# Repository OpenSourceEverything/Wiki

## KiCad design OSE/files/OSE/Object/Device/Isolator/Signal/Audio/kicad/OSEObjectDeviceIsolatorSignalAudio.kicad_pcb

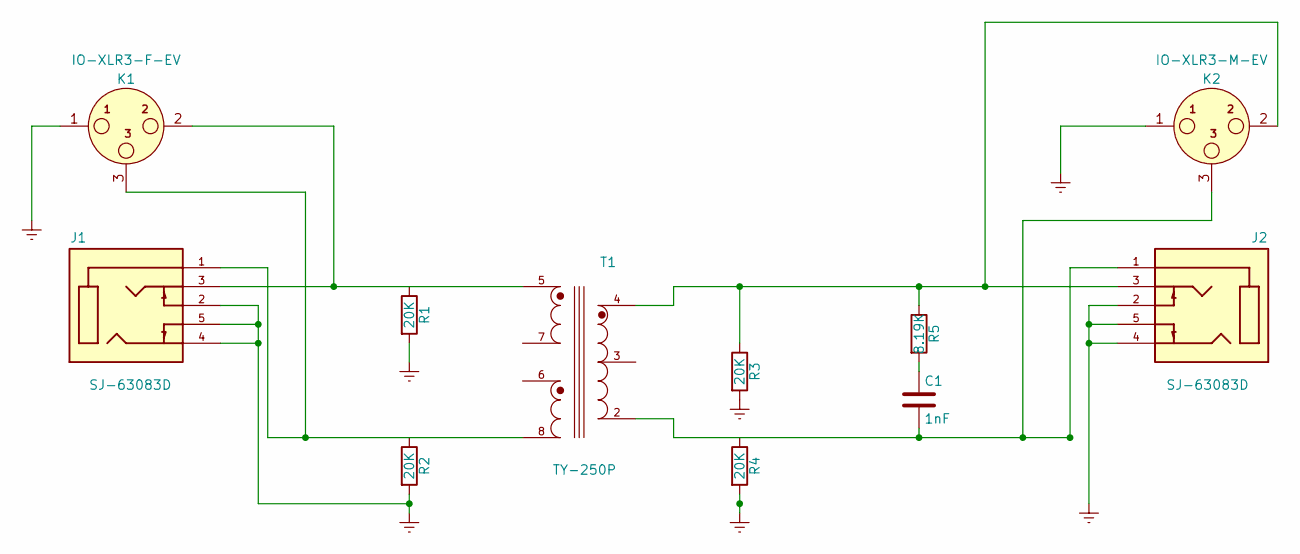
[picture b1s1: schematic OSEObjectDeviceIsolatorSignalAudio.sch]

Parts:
C1: 1nF; C_Disc_D5.0mm_W2.5mm_P2.50mm
J1, J2: SJ-63083D; CUI_SJ-63083D; PARTREV 1.0
K1: IO-XLR3-F-EV; IO-XLR3-{M,F}-EV
K2: IO-XLR3-M-EV; IO-XLR3-{M,F}-EV
R1, R2, R3, R4: 20K; R_Axial_DIN0207_L6.3mm_D2.5mm_P10.16mm_Horizontal
R5: 8.19K; R_Axial_DIN0207_L6.3mm_D2.5mm_P10.16mm_Horizontal
T1: TY-250P; XFMR_TY-250P; PARTREV 2016

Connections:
Earth: J1.2, J1.4, J1.5, J2.2, J2.4, J2.5, K1.1, K2.1, R1.2, R2.2, R3.2, R4.2
unnamed: C1.1, R5.2
unnamed: C1.2, J2.1, K2.3, T1.2
unnamed: J1.1, K1.3, T1.8
unnamed: J1.3, K1.2, T1.5
unnamed: J2.3, K2.2, R3.1, R5.1, T1.4

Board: 2 copper layers, 11 parts (0 on the bottom side), 6 nets, no tracks yet.

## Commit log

2023-02-24 big commit initial of wiki from music machine, moved tthe Object git submodule out of here
2023-02-25 music machine commit
2023-02-25 music machine commit, gitignore changes
2024-05-02 commit from dell
2024-05-22 push from agco windows
2024-05-22 agco comp second
